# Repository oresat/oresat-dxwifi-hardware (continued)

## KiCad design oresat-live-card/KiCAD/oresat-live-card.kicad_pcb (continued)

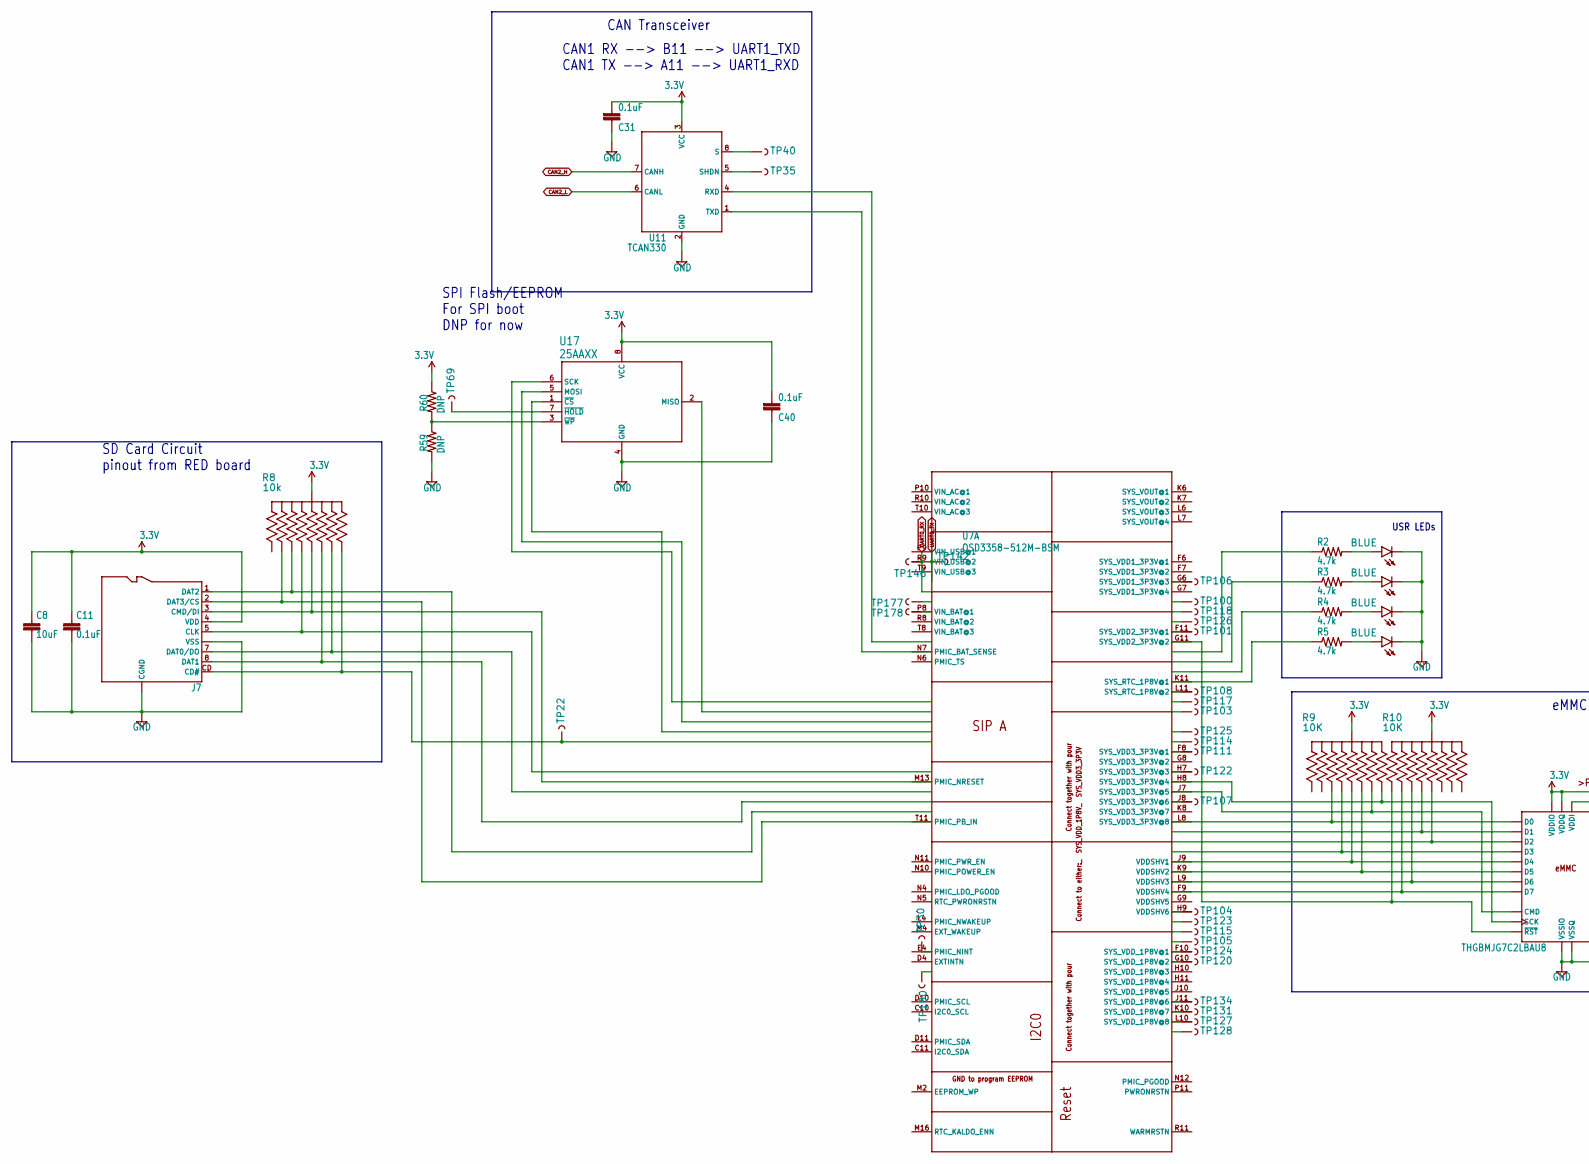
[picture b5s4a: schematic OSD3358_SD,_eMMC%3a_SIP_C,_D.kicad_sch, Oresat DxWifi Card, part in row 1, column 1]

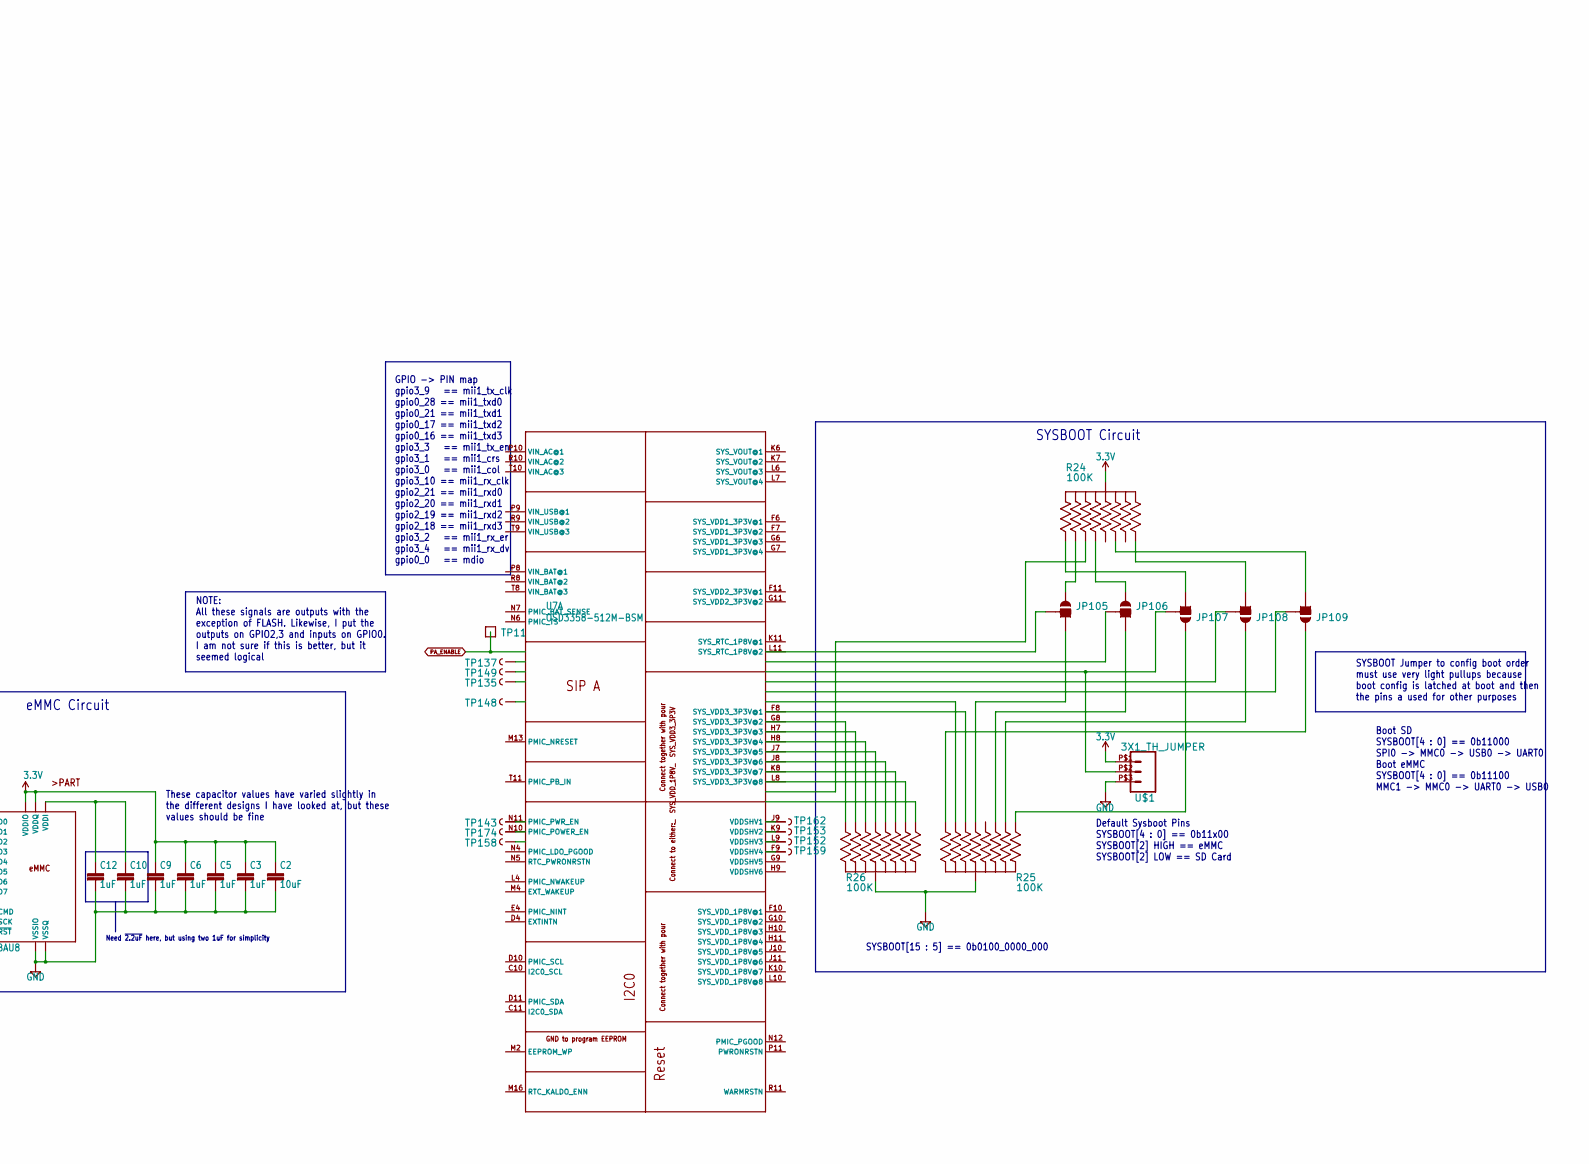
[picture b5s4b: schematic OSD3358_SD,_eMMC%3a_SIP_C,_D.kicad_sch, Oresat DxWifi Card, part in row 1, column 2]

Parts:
C2, C8: 10uF; .0805-B
C3, C5, C6, C9, C10, C12: 1uF; .0603-A
C11, C31, C40: 0.1uF; .0603-A
D2, D3, D4, D5: BLUE; LED-0603
J7: DM3BT-DSF-PEJS
JP105, JP106, JP107, JP108, JP109: JUMPER-SMT_3_1-NC_TRACE_SILK; SMT-JUMPER_3_1-NC_TRACE_SILK
R2, R3, R4, R5: 4.7k; .0603-A
R8: 10K; ARRAY_EXBA-M
R9, R10: EXB-A10P103J; ARRAY_EXBA-M
R24, R25, R26: EXB-A10P104J; ARRAY_EXBA-M
R59, R60: DNP; .0603-A
TP11: TEST-POINT; 2MM-TEST-POINT
TP22, TP30, TP35, TP40, TP69, TP100, TP101, TP103, TP104, TP105, TP106, TP107, TP108, TP111, TP114, TP115, TP117, TP118, TP120, TP122, TP123, TP124, TP125, TP126, TP127, TP128, TP131, TP134, TP135, TP137, TP142, TP143, TP146, TP148, TP149, TP152, TP153, TP158, TP159, TP162, TP174, TP177, TP178, TP180: TEST-POINT3X4; PAD.03X.04
U3: THGBMJG7C2LBAU8; BGA-153(11.5X13)(EMMC-BA)
U7: OSD3358-512M-BSM; OSD335X-BGA-256
U11: TCAN330; SOT23-8_TI-DCN
U17: 25AAXX; SOIC8
U$1: 3X1_TH_JUMPER; 3X1

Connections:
1.8V-A: U7.A7 (SYS_ADC_1P8V), U7.B7 (VREFP), U7.N13 (PMIC_MUX_IN); also elsewhere on the board
3.3V: C2.1, C3.1, C5.1, C6.1, C8.1, C9.1, C11.1, C31.2, C40.2, J7.4 (VDD), R8.5 (55), R8.10 (55), R9.5 (55), R9.10 (55), R10.5 (55), R10.10 (55), R24.5 (55), R24.10 (55), R60.1, U3.C6 (VDDQ), U3.E6 (VDDIO), U3.F5 (VDDIO), U3.J10 (VDDIO), U3.K9 (VDDIO), U3.M4 (VDDQ), U3.N4 (VDDQ), U3.P3 (VDDQ), U3.P5 (VDDQ), U7.F6 (SYS_VDD1_3P3V@1), U7.F7 (SYS_VDD1_3P3V@2), U7.G6 (SYS_VDD1_3P3V@3), U7.G7 (SYS_VDD1_3P3V@4), U11.3 (VCC), U17.8 (VCC), U$1.P$1 (1); also elsewhere on the board
5V: U7.P10 (VIN_AC@1), U7.R10 (VIN_AC@2), U7.T10 (VIN_AC@3); also elsewhere on the board
/OSD3358 PWR, ETC. : SIP A, E, F/N$53: U7.K11 (SYS_RTC_1P8V@1), U7.L11 (SYS_RTC_1P8V@2); also elsewhere on the board
/OSD3358 PWR, ETC. : SIP A, E, F/PMIC_PGOOD: U7.N12 (PMIC_PGOOD), U7.P11 (PWRONRSTN); also elsewhere on the board
/OSD3358 USB, JTAG, XTAL, etc : SIP B/OSC0_GND: U7.N15 (OSC0_GND); also elsewhere on the board
/OSD3358 USB, JTAG, XTAL, etc : SIP B/OSC0_IN: U7.P16 (OSC0_IN); also elsewhere on the board
/OSD3358 USB, JTAG, XTAL, etc : SIP B/OSC0_OUT: U7.N16 (OSC0_OUT); also elsewhere on the board
CAN2_H: U11.7 (CANH); also elsewhere on the board
CAN2_L: U11.6 (CANL); also elsewhere on the board
unnamed: C10.1, C12.1, U3.C2 (VDDI)
unnamed 41: U7.A5 (OSC1_OUT); also elsewhere on the board
unnamed 42: U7.B5 (OSC1_GND); also elsewhere on the board
unnamed 43: U7.A6 (OSC1_IN); also elsewhere on the board
unnamed: D2.A, R2.2
unnamed: D3.A, R3.2
unnamed: D4.A, R4.2
unnamed: D5.A, R5.2
unnamed: J7.1 (DAT2), R8.2 (22), U7.C16 (MMC0_DAT2)
unnamed: J7.2 (DAT3/CS), R8.9 (99), U7.C15 (MMC0_DAT3)
unnamed: J7.3 (CMD/DI), R8.3 (33), U7.B16 (MMC0_CMD)
unnamed: J7.5 (CLK), R8.8 (88), U7.B15 (MMC0_CLK)
unnamed: J7.7 (DAT0/DO), R8.4 (44), U7.A16 (MMC0_DAT0)
unnamed: J7.8 (DAT1), R8.7 (77), U7.A15 (MMC0_DAT1)
unnamed: J7.CD (CD#), R8.6 (66), TP22.1, U7.C14 (SPI0_CS1)
unnamed 77: U7.D2 (TMS); also elsewhere on the board
unnamed 78: U7.D1 (TCK); also elsewhere on the board
unnamed 79: U7.C2 (TDO); also elsewhere on the board
unnamed 80: U7.C1 (TDI); also elsewhere on the board
unnamed 83: U7.L14 (USB1_ID); also elsewhere on the board
unnamed: JP105.1, R24.9 (99)
unnamed: JP105.2, U7.G3 (LCD_DATA0)
unnamed: JP105.3, R25.3 (33)
unnamed: JP106.1, R24.8 (88)
unnamed: JP106.2, U7.G2 (LCD_DATA1)
unnamed: JP106.3, R25.2 (22)
unnamed: JP107.1, R25.1 (11)
unnamed: JP107.2, U7.G1 (LCD_DATA2), U$1.P$2 (2)
unnamed: JP107.3, R24.1 (11)
unnamed: JP108.1, R25.9 (99)
unnamed: JP108.2, U7.H3 (LCD_DATA3)
unnamed: JP108.3, R24.6 (66)
unnamed: JP109.1, R25.6 (66)
unnamed: JP109.2, U7.H2 (LCD_DATA4)
unnamed: JP109.3, R24.7 (77)
unnamed: R2.1, U7.P13 (GPMC_A5)
unnamed: R3.1, U7.T14 (GPMC_A6)
unnamed: R4.1, U7.R14 (GPMC_A7)
unnamed: R5.1, U7.P14 (GPMC_A8)
unnamed: R9.2 (22), U3.A3 (D0), U7.R3 (GPMC_AD0)
unnamed: R9.3 (33), U3.B3 (D4), U7.T2 (GPMC_AD4)
unnamed: R9.4 (44), U3.M5 (CMD), U7.P1 (GPMC_CSN2)
unnamed: R9.6 (66), U3.M6 (SCK), U7.P2 (GPMC_CSN1)
unnamed: R9.7 (77), U3.B4 (D5), U7.T1 (GPMC_AD5)
unnamed: R9.8 (88), U3.B2 (D3), U7.T3 (GPMC_AD3)
unnamed: R10.1 (11), U3.K5 (~RST), U7.R13 (GPMC_A4)
unnamed: R10.2 (22), U3.B5 (D6), U7.P4 (GPMC_AD6)
unnamed: R10.3 (33), U3.A5 (D2), U7.R1 (GPMC_AD2)
unnamed: R10.8 (88), U3.A4 (D1), U7.R2 (GPMC_AD1)
unnamed: R10.9 (99), U3.B6 (D7), U7.R4 (GPMC_AD7)
unnamed 126: U7.M16 (RTC_KALDO_ENN); also elsewhere on the board
unnamed 127: U7.D3 (TRSTN); also elsewhere on the board
unnamed 128: U7.E3 (EMU1); also elsewhere on the board
unnamed 129: U7.E2 (EMU0); also elsewhere on the board
unnamed: R24.2 (22), U7.L1 (LCD_DATA14)
unnamed: R25.4 (44), U7.H1 (LCD_DATA5)
unnamed: R25.7 (77), U7.J3 (LCD_DATA6)
unnamed: R26.1 (11), U7.M3 (LCD_DATA15)
unnamed: R26.2 (22), U7.L3 (LCD_DATA12)
unnamed: R26.3 (33), U7.K2 (LCD_DATA10)
unnamed: R26.4 (44), U7.J1 (LCD_DATA8)
unnamed: R26.6 (66), U7.J2 (LCD_DATA7)
unnamed: R26.7 (77), U7.K3 (LCD_DATA9)
unnamed: R26.8 (88), U7.K1 (LCD_DATA11)
unnamed: R26.9 (99), U7.L2 (LCD_DATA13)
unnamed: R59.1, R60.2, U17.3 (~WP)
unnamed 152: U7.C10 (I2C0_SCL), U7.D10 (PMIC_SCL); also elsewhere on the board
unnamed 153: U7.C11 (I2C0_SDA), U7.D11 (PMIC_SDA); also elsewhere on the board
unnamed 154: U7.M2 (EEPROM_WP); also elsewhere on the board
unnamed 171: U7.F10 (SYS_VDD_1P8V@1), U7.G10 (SYS_VDD_1P8V@2), U7.H10 (SYS_VDD_1P8V@3), U7.H11 (SYS_VDD_1P8V@4), U7.J10 (SYS_VDD_1P8V@5), U7.J11 (SYS_VDD_1P8V@6), U7.K10 (SYS_VDD_1P8V@7), U7.L10 (SYS_VDD_1P8V@8); also elsewhere on the board
unnamed 172: U7.M14 (USB1_DRVVBUS); also elsewhere on the board
unnamed: TP30.1, U7.A4 (XDMA_EVENT_INTR0)
unnamed: TP35.1, U11.5 (SHDN)
unnamed 178: U7.B8 (AIN1); also elsewhere on the board
unnamed 179: U7.A8 (AIN0); also elsewhere on the board
unnamed: TP40.1, U11.8 (S)
unnamed: TP69.1, U17.7 (~HOLD)
unnamed: TP100.1, U7.T12 (GPMC_A0)
unnamed: TP101.1, U7.T13 (GPMC_A3)
unnamed: TP103.1, U7.T16 (GPMC_A11)
unnamed: TP104.1, U7.T4 (GPMC_AD8)
unnamed: TP105.1, U7.T5 (GPMC_AD11)
unnamed: TP106.1, U7.T7 (GPMC_CLK)
unnamed: TP107.1, U7.R7 (GPMC_CSN3)
unnamed: TP108.1, U7.T15 (GPMC_A9)
unnamed: TP111.1, U7.R16 (GPMC_WPN)
unnamed: TP114.1, U7.P15 (GPMC_WAIT0)
unnamed: TP115.1, U7.R5 (GPMC_AD10)
unnamed: TP117.1, U7.R15 (GPMC_A10)
unnamed: TP118.1, U7.R12 (GPMC_A1)
unnamed: TP120.1, U7.R6 (GPMC_AD13)
unnamed: TP122.1, U7.P3 (GPMC_CSN0)
unnamed: TP123.1, U7.P5 (GPMC_AD9)
unnamed: TP124.1, U7.P6 (GPMC_AD12)
unnamed: TP125.1, U7.N14 (GPMC_BEN1)
unnamed: TP126.1, U7.P12 (GPMC_A2)
unnamed: TP127.1, U7.N2 (GPMC_WEN)
unnamed: TP128.1, U7.N1 (GPMC_OEN_REN)
unnamed 206: U7.N6 (PMIC_TS); also elsewhere on the board
unnamed 207: U7.N7 (PMIC_BAT_SENSE), U7.P8 (VIN_BAT@1), U7.R8 (VIN_BAT@2), U7.T8 (VIN_BAT@3); also elsewhere on the board
unnamed: TP131.1, U7.N3 (GPMC_BEN0_CLE)
unnamed: TP134.1, U7.M1 (GPMC_ADVN_ALE)
unnamed: TP135.1, U7.G16 (MII1_TXD2)
unnamed: TP137.1, U7.H15 (MII1_TXD0)
unnamed 212: U7.K14 (USB0_ID); also elsewhere on the board
unnamed 213: U7.J15 (USB0_DRVVBUS); also elsewhere on the board
unnamed 214: U7.K13 (USB0_CE); also elsewhere on the board
unnamed: TP143.1, U7.J14 (RMII1_REF_CLK)
unnamed 216: U7.L13 (USB1_CE); also elsewhere on the board
unnamed 217: U7.K4 (NC@3); also elsewhere on the board
unnamed: TP148.1, U7.G14 (MII1_TX_EN)
unnamed: TP149.1, U7.H14 (MII1_TXD1)
unnamed 220: U7.J6 (NC@2); also elsewhere on the board
unnamed: TP152.1, U7.F2 (LCD_HSYNC)
unnamed: TP153.1, U7.F3 (LCD_VSYNC)
unnamed 223: U7.G4 (VDD_CORE); also elsewhere on the board
unnamed 224: U7.F4 (VDDS_DDR); also elsewhere on the board
unnamed 225: U7.H6 (VPP); also elsewhere on the board
unnamed: TP158.1, U7.E13 (MDIO)
unnamed: TP159.1, U7.E1 (LCD_AC_BIAS_EN)
unnamed 228: U7.F13 (VDD_MPU); also elsewhere on the board
unnamed 229: U7.F11 (SYS_VDD2_3P3V@1), U7.G11 (SYS_VDD2_3P3V@2); also elsewhere on the board
unnamed: TP162.1, U7.F1 (LCD_PCLK)
unnamed 231: U7.G13 (VDDS_PLL); also elsewhere on the board
unnamed 232: U7.D4 (EXTINTN), U7.E4 (PMIC_NINT); also elsewhere on the board
unnamed 233: U7.C8 (AIN5); also elsewhere on the board
unnamed 234: U7.D12 (NC@1); also elsewhere on the board
unnamed 235: U7.D5 (CAP_VDD_RTC); also elsewhere on the board
unnamed: TP174.1, U7.D13 (MDC)
unnamed 237: U7.C6 (AIN3); also elsewhere on the board
unnamed 238: U7.C7 (AIN4); also elsewhere on the board
unnamed: TP177.1, U7.C12 (UART0_CTSN)
unnamed: TP178.1, U7.C13 (UART0_RTSN)
unnamed: TP180.1, U7.C5 (ECAP0_IN_PWM0_OUT)
unnamed 242: U7.B6 (AIN2); also elsewhere on the board
unnamed 243: U7.L15 (USB1_DP); also elsewhere on the board
unnamed 244: U7.L16 (USB1_DM); also elsewhere on the board
unnamed: U7.D6 (PMIC_MUX_OUT), U7.D7 (AIN7)
unnamed: U7.A11 (UART1_RXD), U11.1 (TXD)
unnamed: U7.B11 (UART1_TXD), U11.4 (RXD)
unnamed: U7.A14 (SPI0_CS0), U17.1 (~CS)
unnamed: U7.B13 (SPI0_D0), U17.2 (MISO)
unnamed: U7.B14 (SPI0_D1), U17.5 (MOSI)
unnamed: U7.A13 (SPI0_SCLK), U17.6 (SCK)
PA_ENABLE: TP11.1, U7.H16 (MII1_TX_CLK); also elsewhere on the board
PA_THERMISTOR: U7.C9 (AIN6); also elsewhere on the board
RESET#: U7.R11 (WARMRSTN); also elsewhere on the board
UART0_RX: TP146.1, U7.A12 (UART0_RXD); also elsewhere on the board
UART0_TX: TP142.1, U7.B12 (UART0_TXD); also elsewhere on the board
USB_DEV_N: U7.K16 (USB0_DM); also elsewhere on the board
USB_DEV_P: U7.K15 (USB0_DP); also elsewhere on the board
VDD: U7.K6 (SYS_VOUT@1), U7.K7 (SYS_VOUT@2), U7.L6 (SYS_VOUT@3), U7.L7 (SYS_VOUT@4); also elsewhere on the board
VIN_USB: U7.J16 (USB0_VBUS), U7.P9 (VIN_USB@1), U7.R9 (VIN_USB@2), U7.T9 (VIN_USB@3); also elsewhere on the board

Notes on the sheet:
CAN Transceiver
CAN1 RX --> B11 --> UART1_TXD CAN1 TX --> A11 --> UART1_RXD
USR LEDs
These capacitor values have varied slightly in the different designs I have looked at, but these values should be fine
NOTE: All these signals are outputs with the exception of FLASH. Likewise, I put the outputs on GPIO2,3 and inputs on GPIO0. I am not sure if this is better, but it seemed logical
Need ~{2.2uF} here, but using two 1uF for simplicity
GPIO -> PIN map gpio3_9 == mii1_tx_clk gpio0_28 == mii1_txd0 gpio0_21 == mii1_txd1 gpio0_17 == mii1_txd2 gpio0_16 == mii1_txd3 gpio3_3 == mii1_tx_en gpio3_1 == mii1_crs gpio3_0 == mii1_col gpio3_10 == mii1_rx_clk gpio2_21 == mii1_rxd0 gpio2_20 == mii1_rxd1 gpio2_19 == mii1_rxd2 gpio2_18 == mii1_rxd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
SYSBOOT[15 : 5] == 0b0100_0000_000
Boot SD SYSBOOT[4 : 0] == 0b11000 SPI0 -> MMC0 -> USB0 -> UART0 Boot eMMC SYSBOOT[4 : 0] == 0b11100 MMC1 -> MMC0 -> UART0 -> USB0
SYSBOOT Jumper to config boot order must use very light pullups because boot config is latched at boot and then the pins a used for other purposes
eMMC Circuit
SYSBOOT Circuit
SPI Flash/EEPROM For SPI boot DNP for now
Default Sysboot Pins SYSBOOT[4 : 0] == 0b11x00 SYSBOOT[2] HIGH == eMMC SYSBOOT[2] LOW == SD Card
SD Card Circuit pinout from RED board

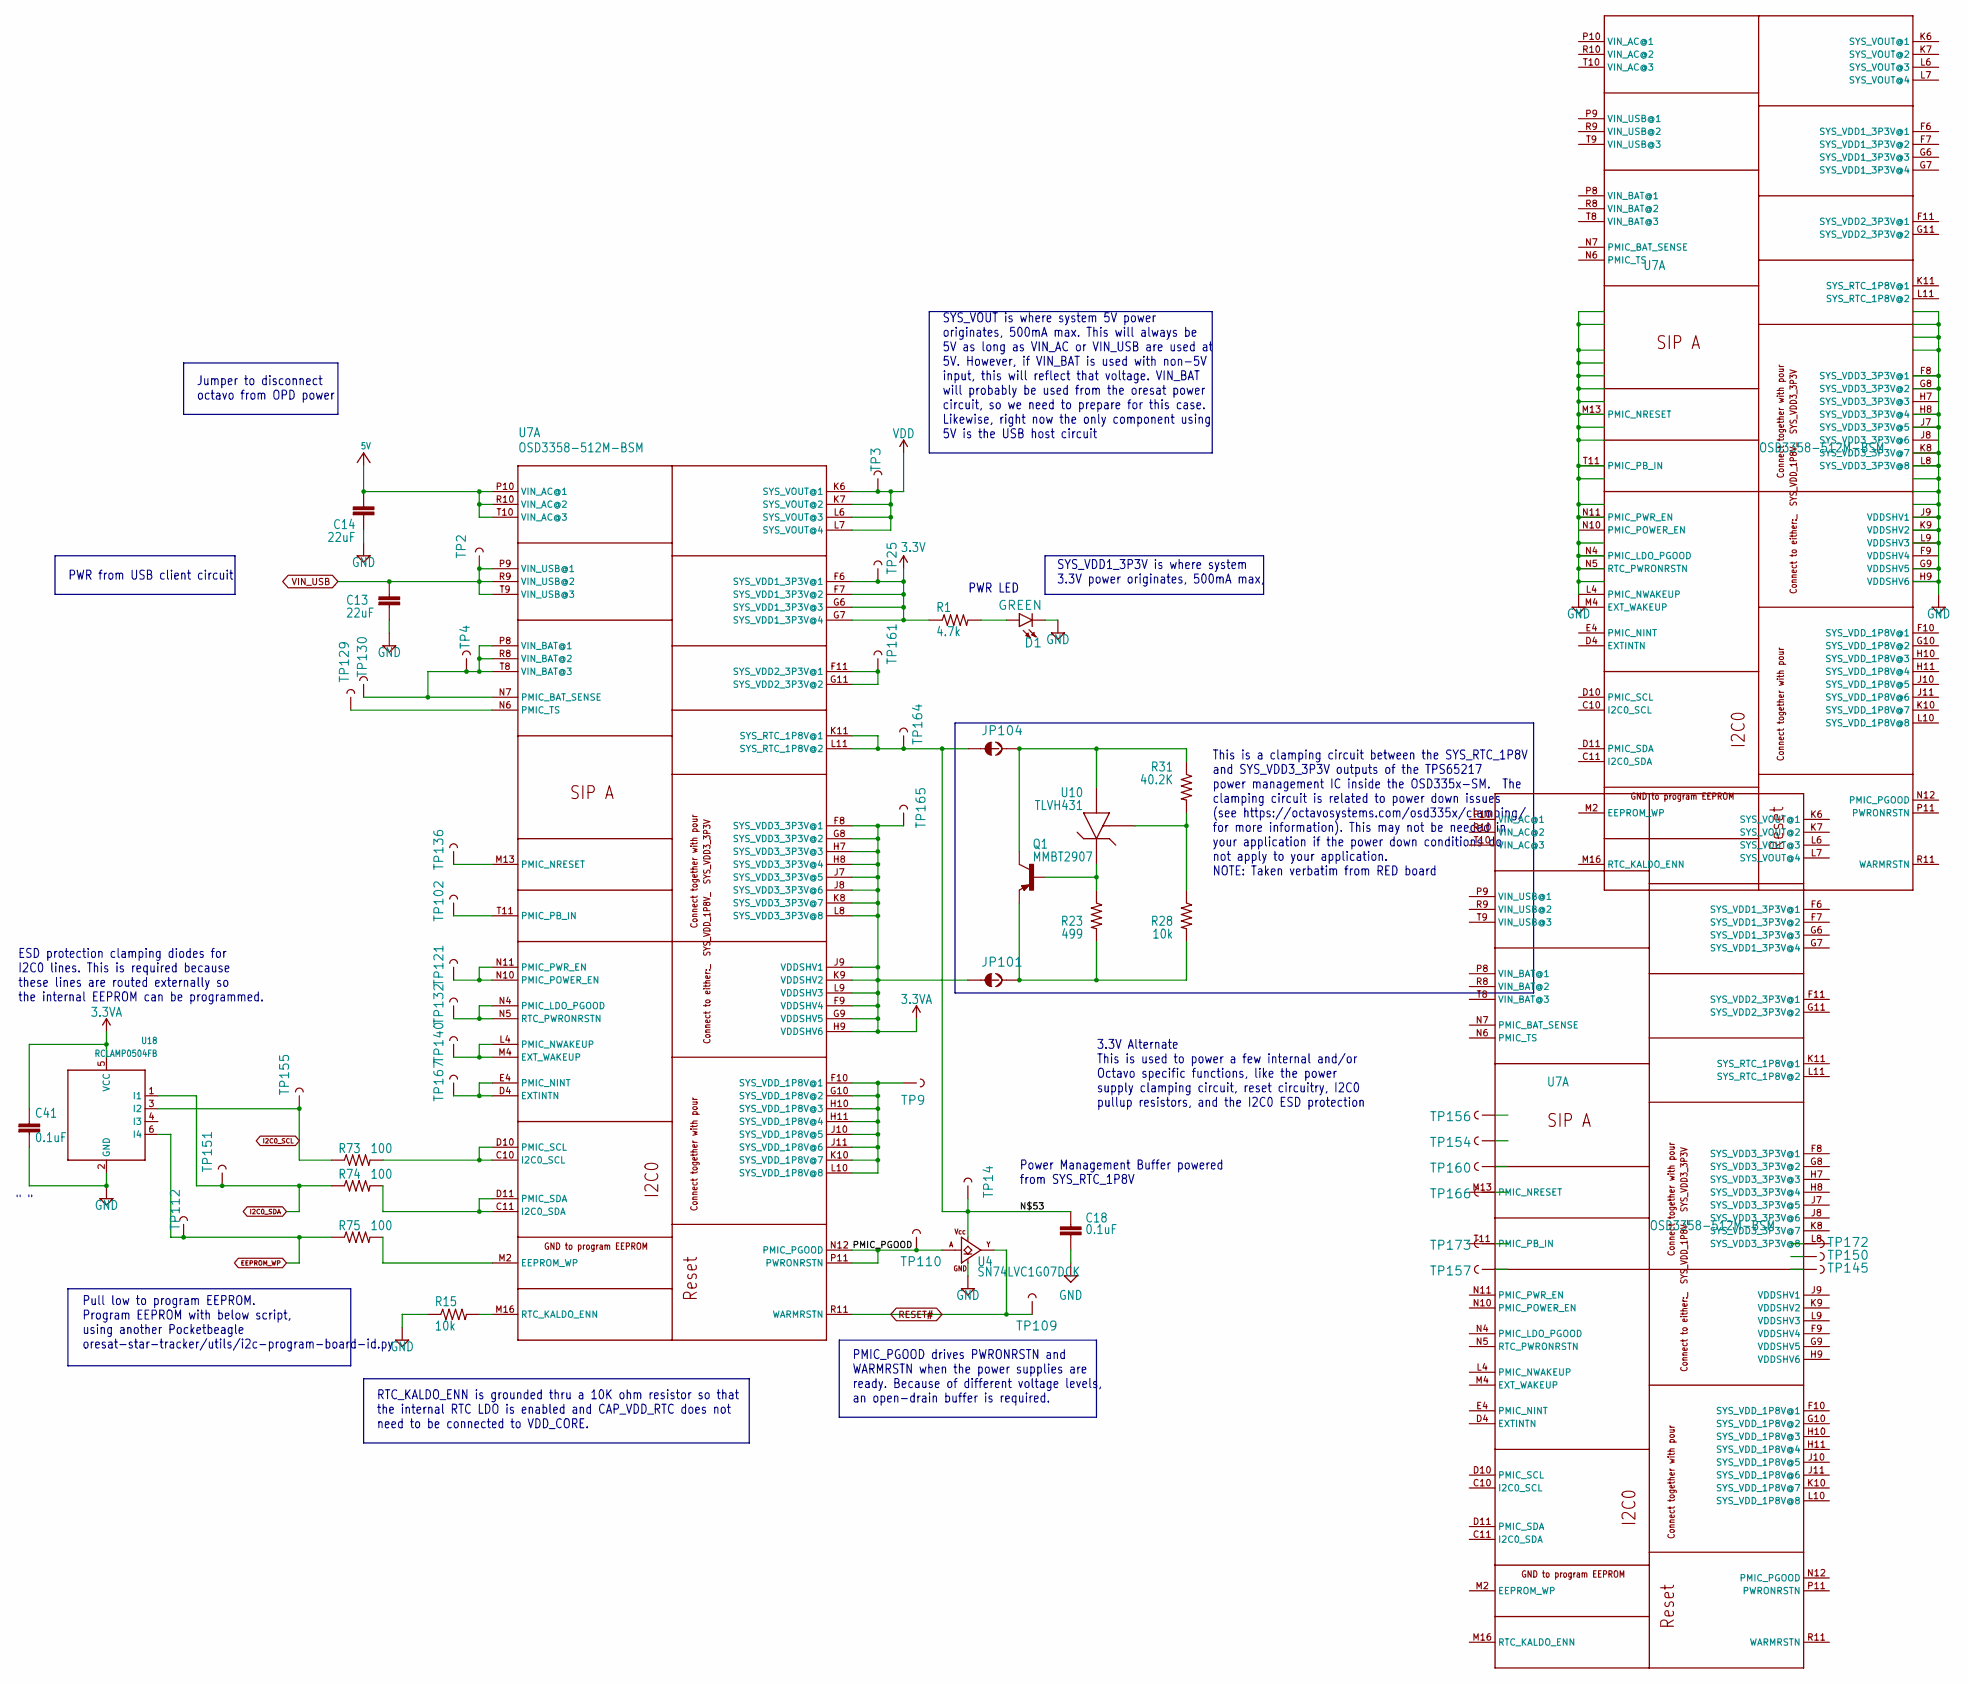
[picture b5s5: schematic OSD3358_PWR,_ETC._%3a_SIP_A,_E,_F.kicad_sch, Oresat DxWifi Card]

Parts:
C13, C14: 22uF; C1210
C18, C41: 0.1uF; .0603-A
D1: 150060VS55040; LED-0603
JP101, JP104: JUMPER-SMT_2_NC_TRACE_SILK; SMT-JUMPER_2_NC_TRACE_SILK
Q1: MMBT2907; SOT23-BEC
R1: 4.7k; .0603-A
R15, R28: 10k; .0603-A
R23: 499; .0603-A
R31: 40.2K; .0603-A
R73, R74, R75: 100; .0603-A
TP2, TP3, TP4, TP9, TP14, TP25, TP102, TP109, TP110, TP112, TP121, TP129, TP130, TP132, TP136, TP140, TP145, TP150, TP151, TP154, TP155, TP156, TP157, TP160, TP161, TP164, TP165, TP166, TP167, TP172, TP173: TEST-POINT3X4; PAD.03X.04
U4: SN74LVC1G07DCK; C70(TI-DCK)
U7: OSD3358-512M-BSM; OSD335X-BGA-256
U10: TLVH431; SOT23-3
U18: RCLAMP0504FB; SC70-6

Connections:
1.8V-A: U7.A7 (SYS_ADC_1P8V), U7.B7 (VREFP), U7.N13 (PMIC_MUX_IN); also elsewhere on the board
3.3V: R1.1, TP25.1, U7.F6 (SYS_VDD1_3P3V@1), U7.F7 (SYS_VDD1_3P3V@2), U7.G6 (SYS_VDD1_3P3V@3), U7.G7 (SYS_VDD1_3P3V@4); also elsewhere on the board
5V: C14.1, U7.P10 (VIN_AC@1), U7.R10 (VIN_AC@2), U7.T10 (VIN_AC@3); also elsewhere on the board
/OSD3358 PWR, ETC. : SIP A, E, F/N$53: C18.1, JP104.1, TP14.1, TP164.1, U4.5 (VCC), U7.K11 (SYS_RTC_1P8V@1), U7.L11 (SYS_RTC_1P8V@2)
/OSD3358 PWR, ETC. : SIP A, E, F/PMIC_PGOOD: TP110.1, U4.2 (A), U7.N12 (PMIC_PGOOD), U7.P11 (PWRONRSTN)
/OSD3358 USB, JTAG, XTAL, etc : SIP B/OSC0_GND: U7.N15 (OSC0_GND); also elsewhere on the board
/OSD3358 USB, JTAG, XTAL, etc : SIP B/OSC0_IN: U7.P16 (OSC0_IN); also elsewhere on the board
/OSD3358 USB, JTAG, XTAL, etc : SIP B/OSC0_OUT: U7.N16 (OSC0_OUT); also elsewhere on the board
EEPROM_WP: R75.1, TP112.1, U18.6 (I4); also elsewhere on the board
I2C0_SCL: R73.1, TP155.1, U18.3 (I2); also elsewhere on the board
I2C0_SDA: R74.1, TP151.1, U18.1 (I1); also elsewhere on the board
unnamed 41: U7.A5 (OSC1_OUT); also elsewhere on the board
unnamed 42: U7.B5 (OSC1_GND); also elsewhere on the board
unnamed 43: U7.A6 (OSC1_IN); also elsewhere on the board
unnamed: D1.A, R1.2
unnamed 70: U7.C16 (MMC0_DAT2); also elsewhere on the board
unnamed 71: U7.C15 (MMC0_DAT3); also elsewhere on the board
unnamed 72: U7.B16 (MMC0_CMD); also elsewhere on the board
unnamed 73: U7.B15 (MMC0_CLK); also elsewhere on the board
unnamed 74: U7.A16 (MMC0_DAT0); also elsewhere on the board
unnamed 75: U7.A15 (MMC0_DAT1); also elsewhere on the board
unnamed 76: U7.C14 (SPI0_CS1); also elsewhere on the board
unnamed 77: U7.D2 (TMS); also elsewhere on the board
unnamed 78: U7.D1 (TCK); also elsewhere on the board
unnamed 79: U7.C2 (TDO); also elsewhere on the board
unnamed 80: U7.C1 (TDI); also elsewhere on the board
unnamed 83: U7.L14 (USB1_ID); also elsewhere on the board
unnamed: JP101.2, Q1.E, R23.2, R28.2
unnamed: JP104.2, Q1.C, R31.1, U10.3 (ANODE)
unnamed 87: U7.G3 (LCD_DATA0); also elsewhere on the board
unnamed 90: U7.G2 (LCD_DATA1); also elsewhere on the board
unnamed 93: U7.G1 (LCD_DATA2); also elsewhere on the board
unnamed 96: U7.H3 (LCD_DATA3); also elsewhere on the board
unnamed 99: U7.H2 (LCD_DATA4); also elsewhere on the board
unnamed: Q1.B, R23.1, U10.2 (CATHODE)
unnamed 108: U7.P13 (GPMC_A5); also elsewhere on the board
unnamed 109: U7.T14 (GPMC_A6); also elsewhere on the board
unnamed 110: U7.R14 (GPMC_A7); also elsewhere on the board
unnamed 111: U7.P14 (GPMC_A8); also elsewhere on the board
unnamed 114: U7.R3 (GPMC_AD0); also elsewhere on the board
unnamed 115: U7.T2 (GPMC_AD4); also elsewhere on the board
unnamed 116: U7.P1 (GPMC_CSN2); also elsewhere on the board
unnamed 117: U7.P2 (GPMC_CSN1); also elsewhere on the board
unnamed 118: U7.T1 (GPMC_AD5); also elsewhere on the board
unnamed 119: U7.T3 (GPMC_AD3); also elsewhere on the board
unnamed 120: U7.R13 (GPMC_A4); also elsewhere on the board
unnamed 121: U7.P4 (GPMC_AD6); also elsewhere on the board
unnamed 122: U7.R1 (GPMC_AD2); also elsewhere on the board
unnamed 123: U7.R2 (GPMC_AD1); also elsewhere on the board
unnamed 124: U7.R4 (GPMC_AD7); also elsewhere on the board
unnamed: R15.2, U7.M16 (RTC_KALDO_ENN)
unnamed 127: U7.D3 (TRSTN); also elsewhere on the board
unnamed 128: U7.E3 (EMU1); also elsewhere on the board
unnamed 129: U7.E2 (EMU0); also elsewhere on the board
unnamed 130: U7.L1 (LCD_DATA14); also elsewhere on the board
unnamed 131: U7.H1 (LCD_DATA5); also elsewhere on the board
unnamed 132: U7.J3 (LCD_DATA6); also elsewhere on the board
unnamed 133: U7.M3 (LCD_DATA15); also elsewhere on the board
unnamed 134: U7.L3 (LCD_DATA12); also elsewhere on the board
unnamed 135: U7.K2 (LCD_DATA10); also elsewhere on the board
unnamed 136: U7.J1 (LCD_DATA8); also elsewhere on the board
unnamed 137: U7.J2 (LCD_DATA7); also elsewhere on the board
unnamed 138: U7.K3 (LCD_DATA9); also elsewhere on the board
unnamed 139: U7.K1 (LCD_DATA11); also elsewhere on the board
unnamed 140: U7.L2 (LCD_DATA13); also elsewhere on the board
unnamed: R28.1, R31.2, U10.1 (REF)
unnamed: R73.2, U7.C10 (I2C0_SCL), U7.D10 (PMIC_SCL)
unnamed: R74.2, U7.C11 (I2C0_SDA), U7.D11 (PMIC_SDA)
unnamed: R75.2, U7.M2 (EEPROM_WP)
unnamed: TP9.1, U7.F10 (SYS_VDD_1P8V@1), U7.G10 (SYS_VDD_1P8V@2), U7.H10 (SYS_VDD_1P8V@3), U7.H11 (SYS_VDD_1P8V@4), U7.J10 (SYS_VDD_1P8V@5), U7.J11 (SYS_VDD_1P8V@6), U7.K10 (SYS_VDD_1P8V@7), U7.L10 (SYS_VDD_1P8V@8)
unnamed 172: U7.M14 (USB1_DRVVBUS); also elsewhere on the board
unnamed 176: U7.A4 (XDMA_EVENT_INTR0); also elsewhere on the board
unnamed 178: U7.B8 (AIN1); also elsewhere on the board
unnamed 179: U7.A8 (AIN0); also elsewhere on the board
unnamed 185: U7.T12 (GPMC_A0); also elsewhere on the board
unnamed 186: U7.T13 (GPMC_A3); also elsewhere on the board
unnamed 187: U7.T16 (GPMC_A11); also elsewhere on the board
unnamed 188: U7.T4 (GPMC_AD8); also elsewhere on the board
unnamed 189: U7.T5 (GPMC_AD11); also elsewhere on the board
unnamed 190: U7.T7 (GPMC_CLK); also elsewhere on the board
unnamed 191: U7.R7 (GPMC_CSN3); also elsewhere on the board
unnamed 192: U7.T15 (GPMC_A9); also elsewhere on the board
unnamed 193: U7.R16 (GPMC_WPN); also elsewhere on the board
unnamed 194: U7.P15 (GPMC_WAIT0); also elsewhere on the board
unnamed 195: U7.R5 (GPMC_AD10); also elsewhere on the board
unnamed 196: U7.R15 (GPMC_A10); also elsewhere on the board
unnamed 197: U7.R12 (GPMC_A1); also elsewhere on the board
unnamed 198: U7.R6 (GPMC_AD13); also elsewhere on the board
unnamed 199: U7.P3 (GPMC_CSN0); also elsewhere on the board
unnamed 200: U7.P5 (GPMC_AD9); also elsewhere on the board
unnamed 201: U7.P6 (GPMC_AD12); also elsewhere on the board
unnamed 202: U7.N14 (GPMC_BEN1); also elsewhere on the board
unnamed 203: U7.P12 (GPMC_A2); also elsewhere on the board
unnamed 204: U7.N2 (GPMC_WEN); also elsewhere on the board
unnamed 205: U7.N1 (GPMC_OEN_REN); also elsewhere on the board
unnamed: TP129.1, U7.N6 (PMIC_TS)
unnamed: TP4.1, TP130.1, U7.N7 (PMIC_BAT_SENSE), U7.P8 (VIN_BAT@1), U7.R8 (VIN_BAT@2), U7.T8 (VIN_BAT@3)
unnamed 208: U7.N3 (GPMC_BEN0_CLE); also elsewhere on the board
unnamed 209: U7.M1 (GPMC_ADVN_ALE); also elsewhere on the board
unnamed 210: U7.G16 (MII1_TXD2); also elsewhere on the board
unnamed 211: U7.H15 (MII1_TXD0); also elsewhere on the board
unnamed 212: U7.K14 (USB0_ID); also elsewhere on the board
unnamed 213: U7.J15 (USB0_DRVVBUS); also elsewhere on the board
unnamed 214: U7.K13 (USB0_CE); also elsewhere on the board
unnamed 215: U7.J14 (RMII1_REF_CLK); also elsewhere on the board
unnamed 216: U7.L13 (USB1_CE); also elsewhere on the board
unnamed: TP145.1, U7.K4 (NC@3)
unnamed 218: U7.G14 (MII1_TX_EN); also elsewhere on the board
unnamed 219: U7.H14 (MII1_TXD1); also elsewhere on the board
unnamed: TP150.1, U7.J6 (NC@2)
unnamed 221: U7.F2 (LCD_HSYNC); also elsewhere on the board
unnamed 222: U7.F3 (LCD_VSYNC); also elsewhere on the board
unnamed: TP154.1, U7.G4 (VDD_CORE)
unnamed: TP156.1, U7.F4 (VDDS_DDR)
unnamed: TP157.1, U7.H6 (VPP)
unnamed 226: U7.E13 (MDIO); also elsewhere on the board
unnamed 227: U7.E1 (LCD_AC_BIAS_EN); also elsewhere on the board
unnamed: TP160.1, U7.F13 (VDD_MPU)
unnamed: TP161.1, U7.F11 (SYS_VDD2_3P3V@1), U7.G11 (SYS_VDD2_3P3V@2)
unnamed 230: U7.F1 (LCD_PCLK); also elsewhere on the board
unnamed: TP166.1, U7.G13 (VDDS_PLL)
unnamed: TP167.1, U7.D4 (EXTINTN), U7.E4 (PMIC_NINT)
unnamed 233: U7.C8 (AIN5); also elsewhere on the board
unnamed: TP172.1, U7.D12 (NC@1)
unnamed: TP173.1, U7.D5 (CAP_VDD_RTC)
unnamed 236: U7.D13 (MDC); also elsewhere on the board
unnamed 237: U7.C6 (AIN3); also elsewhere on the board
unnamed 238: U7.C7 (AIN4); also elsewhere on the board
unnamed 239: U7.C12 (UART0_CTSN); also elsewhere on the board
unnamed 240: U7.C13 (UART0_RTSN); also elsewhere on the board
unnamed 241: U7.C5 (ECAP0_IN_PWM0_OUT); also elsewhere on the board
unnamed 242: U7.B6 (AIN2); also elsewhere on the board
unnamed 243: U7.L15 (USB1_DP); also elsewhere on the board
unnamed 244: U7.L16 (USB1_DM); also elsewhere on the board
unnamed: U7.D6 (PMIC_MUX_OUT), U7.D7 (AIN7)
unnamed 250: U7.A11 (UART1_RXD); also elsewhere on the board
unnamed 251: U7.B11 (UART1_TXD); also elsewhere on the board
unnamed 252: U7.A14 (SPI0_CS0); also elsewhere on the board
unnamed 253: U7.B13 (SPI0_D0); also elsewhere on the board
unnamed 254: U7.B14 (SPI0_D1); also elsewhere on the board
unnamed 255: U7.A13 (SPI0_SCLK); also elsewhere on the board
PA_ENABLE: U7.H16 (MII1_TX_CLK); also elsewhere on the board
PA_THERMISTOR: U7.C9 (AIN6); also elsewhere on the board
RESET#: TP109.1, U4.4 (Y), U7.R11 (WARMRSTN); also elsewhere on the board
UART0_RX: U7.A12 (UART0_RXD); also elsewhere on the board
UART0_TX: U7.B12 (UART0_TXD); also elsewhere on the board
USB_DEV_N: U7.K16 (USB0_DM); also elsewhere on the board
USB_DEV_P: U7.K15 (USB0_DP); also elsewhere on the board
VDD: TP3.1, U7.K6 (SYS_VOUT@1), U7.K7 (SYS_VOUT@2), U7.L6 (SYS_VOUT@3), U7.L7 (SYS_VOUT@4)
VIN_USB: C13.1, TP2.1, U7.J16 (USB0_VBUS), U7.P9 (VIN_USB@1), U7.R9 (VIN_USB@2), U7.T9 (VIN_USB@3); also elsewhere on the board

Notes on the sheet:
PWR LED
Power Management Buffer powered from SYS_RTC_1P8V
ESD protection clamping diodes for I2C0 lines. This is required because these lines are routed externally so the internal EEPROM can be programmed.
RTC_KALDO_ENN is grounded thru a 10K ohm resistor so that the internal RTC LDO is enabled and CAP_VDD_RTC does not need to be connected to VDD_CORE.
SYS_VDD1_3P3V is where system 3.3V power originates, 500mA max,
PWR from USB client circuit
This is a clamping circuit between the SYS_RTC_1P8V and SYS_VDD3_3P3V outputs of the TPS65217 power management IC inside the OSD335x-SM. The clamping circuit is related to power down issues (see https://octavosystems.com/osd335x/clamping/ for more information). This may not be needed in your applic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
SYS_VOUT is where system 5V power originates, 500mA max. This will always be 5V as long as VIN_AC or VIN_USB are used at 5V. However, if VIN_BAT is used with non-5V input, this will reflect that voltage. VIN_BAT will probably be used from the oresat power circuit, so we need to prepare for this cas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
3.3V Alternate This is used to power a few internal and/or Octavo specific functions, like the power supply clamping circuit, reset circuitry, I2C0 pullup resistors, and the I2C0 ESD protection
PMIC_PGOOD drives PWRONRSTN and WARMRSTN when the power supplies are ready. Because of different voltage levels, an open-drain buffer is required.
Pull low to program EEPROM. Program EEPROM with below script, using another Pocketbeagle oresat-star-tracker/utils/i2c-program-board-id.py
Jumper to disconnect octavo from OPD power
" "
